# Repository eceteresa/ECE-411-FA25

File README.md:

# ECE 411 Fall 2025 Capstone
Hi hello! Welcome to our capstone. Please review software tools used and some tutorials for how to use said tools. :D

## Tools!

Here are the basic programs you'll need to have on your computer in order to interface with the projects:

- [VSCode](https://code.visualstudio.com/download): A helpful all-in-one programming IDE. Free!
      - You can install the [PlatformIO](https://docs.platformio.org/en/latest/integration/ide/vscode.html) extension and code .ino directly into the IDE!
- [Arduino IDE](https://www.arduino.cc/en/software/): If you would rather not use VSCode.
- Github: Not required, but _strongly_ recommended for ease of file sharing between machines. You can even work from your repo within VSCode using git bash!

### Github Onboarding Crash Course

[Github Setup](https://docs.github.com/en/get-started/git-basics/set-up-git)

[Using Git Graphical User Interface (GUI)](https://www.geeksforgeeks.org/git/working-on-git-for-gui/)

[Github markdown text cheat sheet](https://docs.github.com/en/get-started/writing-on-github/getting-started-with-writing-and-formatting-on-github/basic-writing-and-formatting-syntax)

[What are Git branches and why are they important](https://git-scm.com/book/en/v2/Git-Branching-Branches-in-a-Nutshell)

### Github Task Tracker

[Git Project Tracker Tutorial](https://docs.github.com/en/issues/planning-and-tracking-with-projects/learning-about-projects/quickstart-for-projects)
This tutorial should help you get familiar with how to use the task tracking board under "Projects" in the linked menu up above. There is a kanban template available, so it mimics what Trello can do almost exactly, if not better. The table layout was used so that it's a little easier to see who is assigned to what, and as I (Teresa) poke around with the task tracker it should be pretty intuitive to assign tasks and whatnot. And we don't have to worry about the Trello contributor limit for free accounts.

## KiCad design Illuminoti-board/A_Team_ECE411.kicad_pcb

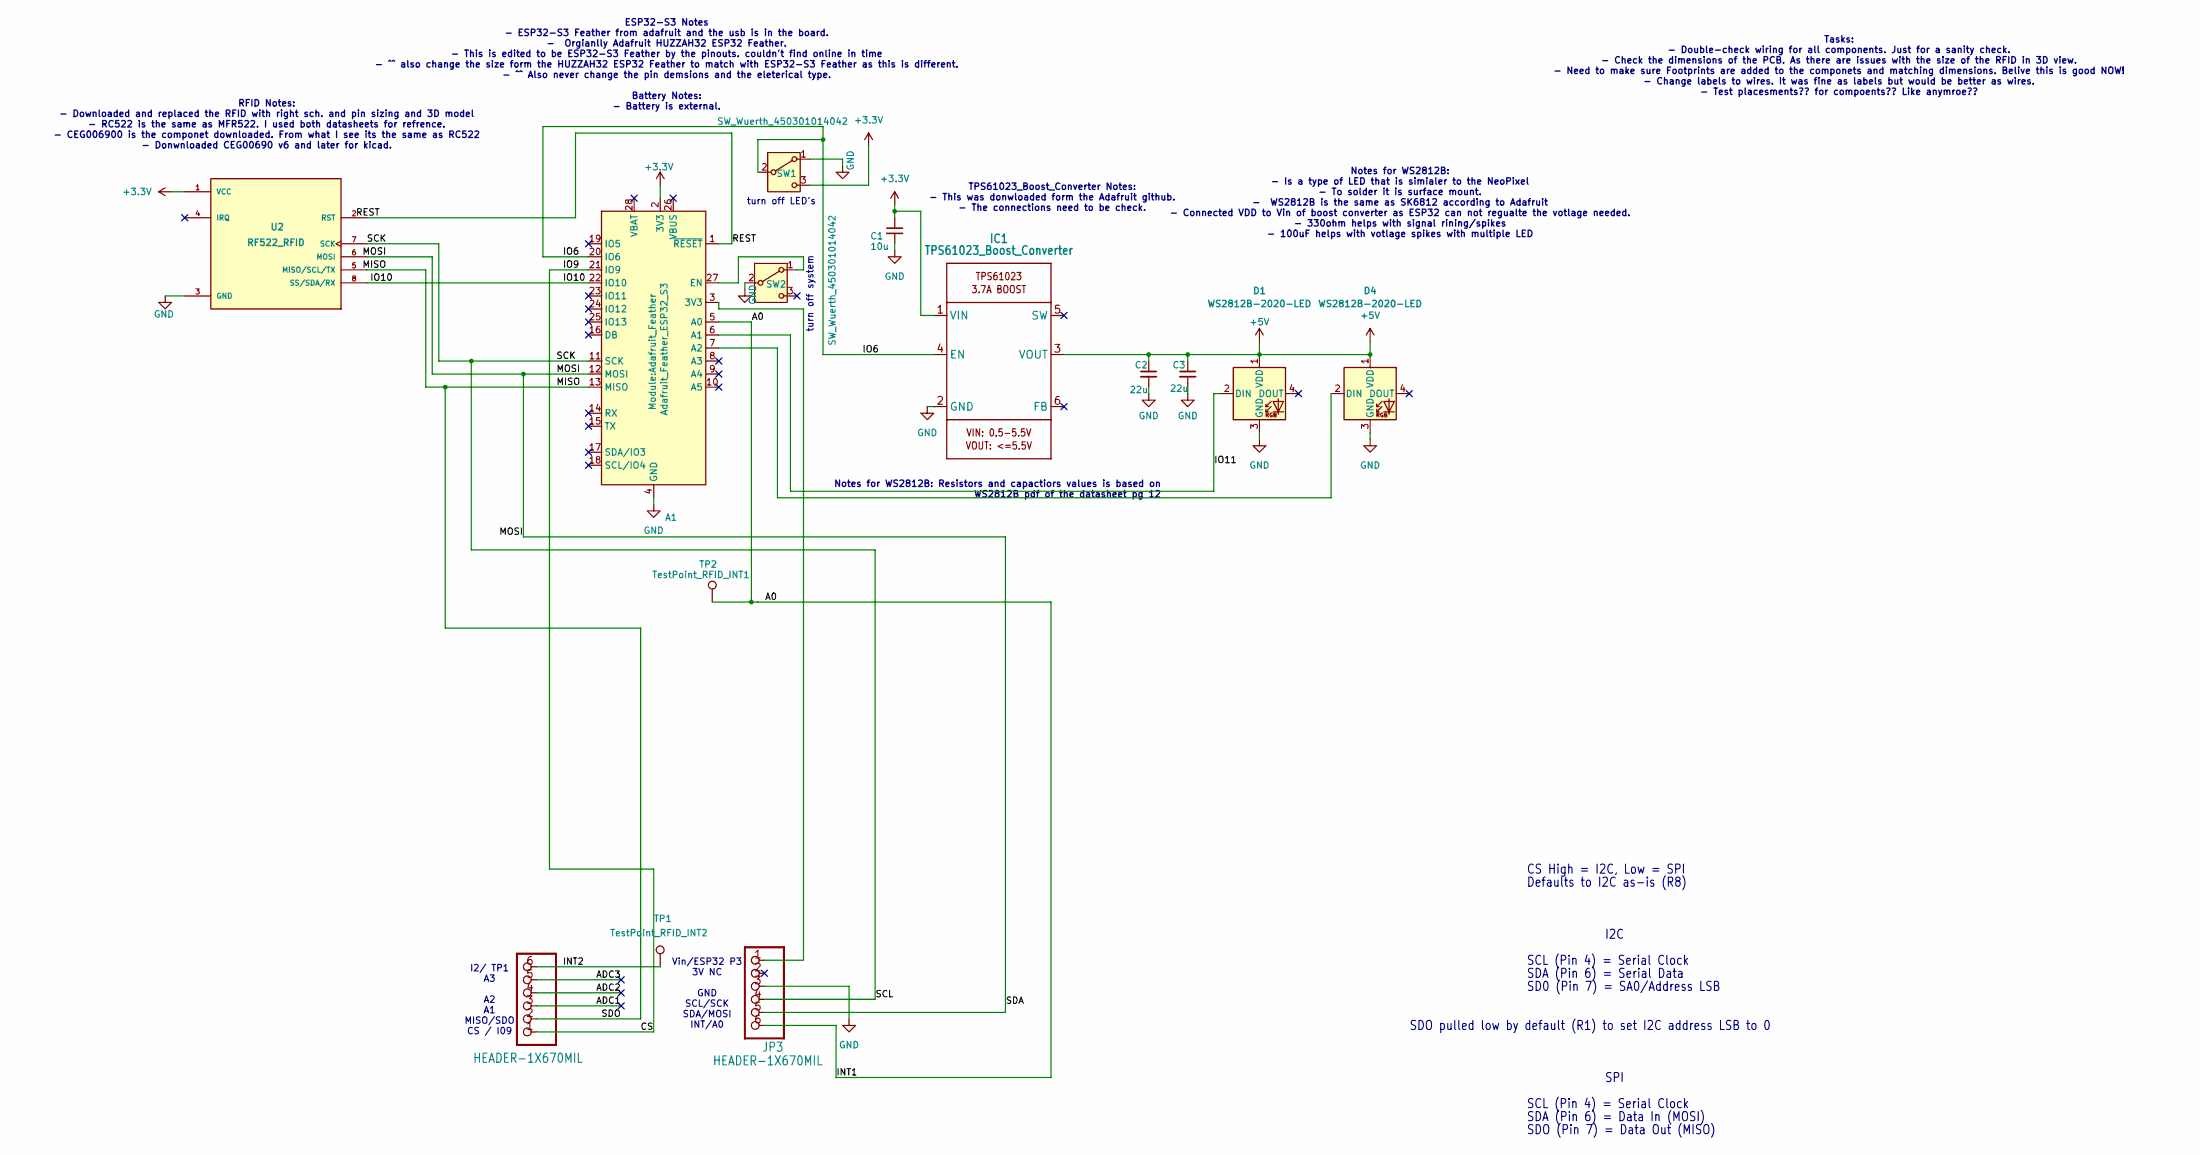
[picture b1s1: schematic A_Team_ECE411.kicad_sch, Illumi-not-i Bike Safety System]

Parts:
A1: Adafruit_Feather_ESP32_S3; Adafruit_Feather
C1: 10u; C_1206_3216Metric_Pad1.33x1.80mm_HandSolder; Part number 399-15735-2-ND
C2, C3: 22u; C_1206_3216Metric_Pad1.33x1.80mm_HandSolder; Part number 581-KGM31AR71A226MU
D1, D4: WS2812B-2020-LED; PinHeader_1x03_P2.54mm_Vertical; Part number 2552
IC1: TPS61023_Boost_Converter; PinHeader_1x04_P2.54mm_Vertical; Part number 4654
JP2, JP3: HEADER-1X670MIL; PinHeader_1x06_P2.54mm_Vertical
SW1, SW2: SW_Wuerth_450301014042; PinHeader_1x03_P2.54mm_Vertical
TP1: TestPoint_RFID_INT2; TestPoint_THTPad_1.0x1.0mm_Drill0.5mm
TP2: TestPoint_RFID_INT1; TestPoint_THTPad_1.0x1.0mm_Drill0.5mm
U2: RF522_RFID; PinHeader_1x08_P2.54mm_Vertical; PARTREV 12 June 2019

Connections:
+3.3V: A1.2 (3V3), C1.1, IC1.1 (VIN), SW1.3 (3V), U2.1 (VCC)
+5V: C2.1, C3.1, D1.1 (VDD), D4.1 (VDD), IC1.3 (VOUT)
/A0: A1.5 (A0), JP3.6, TP2.1
/ADC1: JP2.3
/ADC2: JP2.4
/ADC3: JP2.5
/CS: A1.21 (IO9), JP2.1
/INT2: JP2.6, TP1.1
/IO6: A1.20 (IO6), IC1.4 (EN), SW1.2 (B)
/IO10: A1.22 (IO10), U2.8 (SS/SDA/RX)
/IO11: A1.6 (A1), D1.2 (DIN)
/MISO: A1.13 (MISO), JP2.2, U2.5 (MISO/SCL/TX)
/MOSI: A1.12 (MOSI), JP3.5, U2.6 (MOSI)
/REST: A1.1 (~RESET), U2.2 (RST)
/SCK: A1.11 (SCK), JP3.4, U2.7 (SCK)
GND: A1.4 (GND), C1.2, C2.2, C3.2, D1.3 (GND), D4.3 (GND), IC1.2 (GND), JP3.3, SW1.1 (GND), SW2.2 (B), U2.3 (GND)
unnamed: A1.3 (3V3), JP3.1
unnamed: A1.7 (A2), D4.2 (DIN)
unnamed: A1.27 (EN), SW2.1 (A)

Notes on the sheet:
Tasks: - Double-check wiring for all components. Just for a sanity check. - Check the dimensions of the PCB. As there are issues with the size of the RFID in 3D view. - Need to make sure Footprints are added to the componets and matching dimensions. Belive this is good NOW! - Change labels to wires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
SDO (Pin 7) = Data Out (MISO)
SDA (Pin 6) = Data In (MOSI)
SCL (Pin 4) = Serial Clock
I2/ TP1 A3 A2 A1 MISO/SDO CS / I09
SPI
SD0 (Pin 7) = SA0/Address LSB
ESP32-S3 Notes - ESP32-S3 Feather from adafruit and the usb is in the board. - Orgianlly Adafruit HUZZAH32 ESP32 Feather. - This is edited to be ESP32-S3 Feather by the pinouts. couldn't find online in time - ^^ also change the size form the HUZZAH32 ESP32 Feather to match with ESP32-S3 Feather as 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
SDO pulled low by default (R1) to set I2C address LSB to 0
TPS61023_Boost_Converter Notes: - This was donwloaded form the Adafruit github. - The connections need to be check.
Notes for WS2812B: - Is a type of LED that is simialer to the NeoPixel - To solder it is surface mount. - WS2812B is the same as SK6812 according to Adafruit - Connected VDD to Vin of boost converter as ESP32 can not regualte the votlage needed. - 330ohm helps with signal rining/spikes - 100uF help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
Vin/ESP32 P3 3V NC GND SCL/SCK SDA/MOSI INT/A0
Defaults to I2C as-is (R8)
SDA (Pin 6) = Serial Data
turn off LED's
turn off system
Notes for WS2812B: Resistors and capactiors values is based on WS2812B pdf of the datasheet pg 12
CS High = I2C, Low = SPI
RFID Notes: - Downloaded and replaced the RFID with right sch. and pin sizing and 3D model - RC522 is the same as MFR522. I used both datasheets for refrence. - CEG006900 is the componet downloaded. From what I see its the same as RC522 - Donwnloaded CEG00690 v6 and later for kicad.
I2C

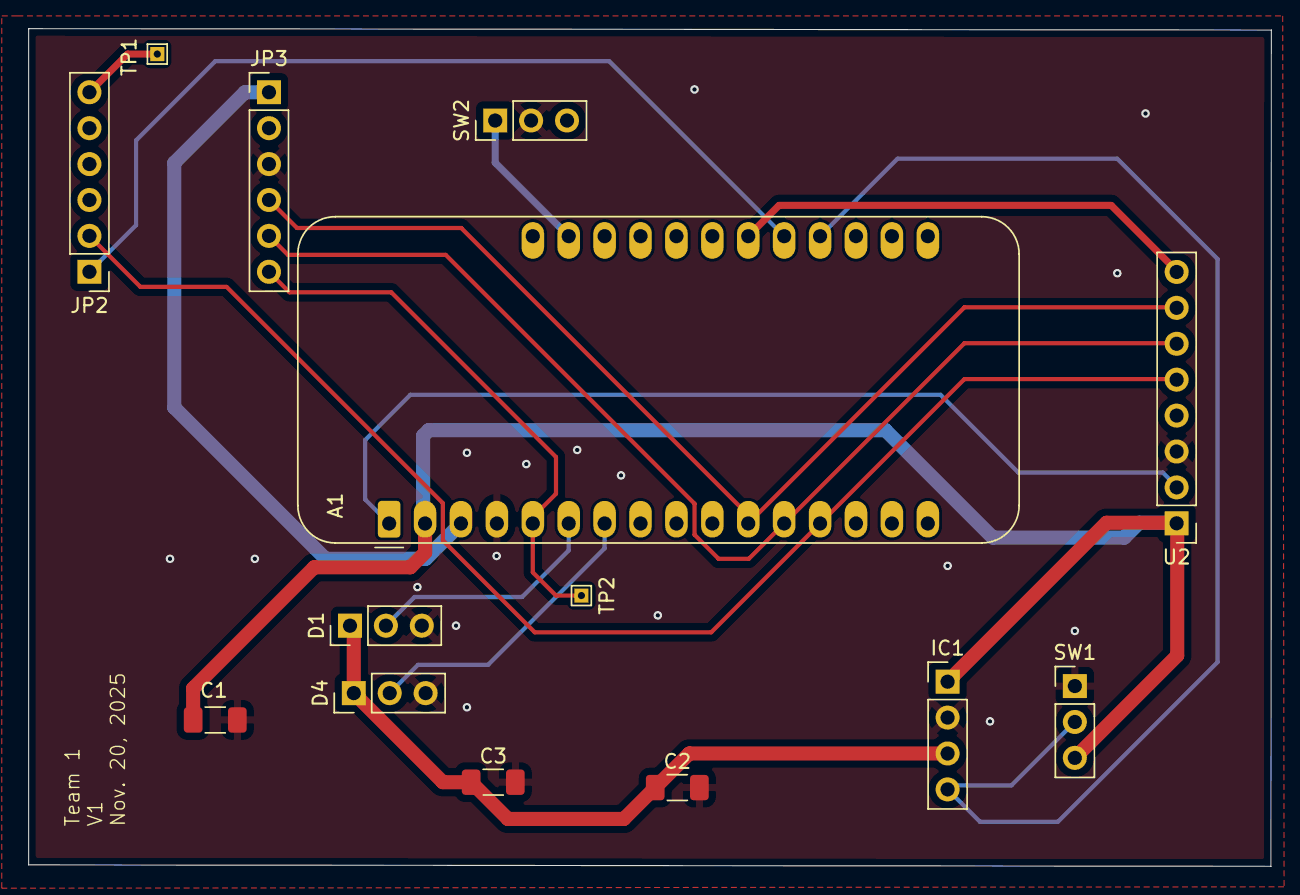
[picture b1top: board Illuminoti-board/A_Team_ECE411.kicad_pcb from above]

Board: 2 copper layers, 87.9 x 59.2 mm, 14 parts (0 on the bottom side), 16 nets.

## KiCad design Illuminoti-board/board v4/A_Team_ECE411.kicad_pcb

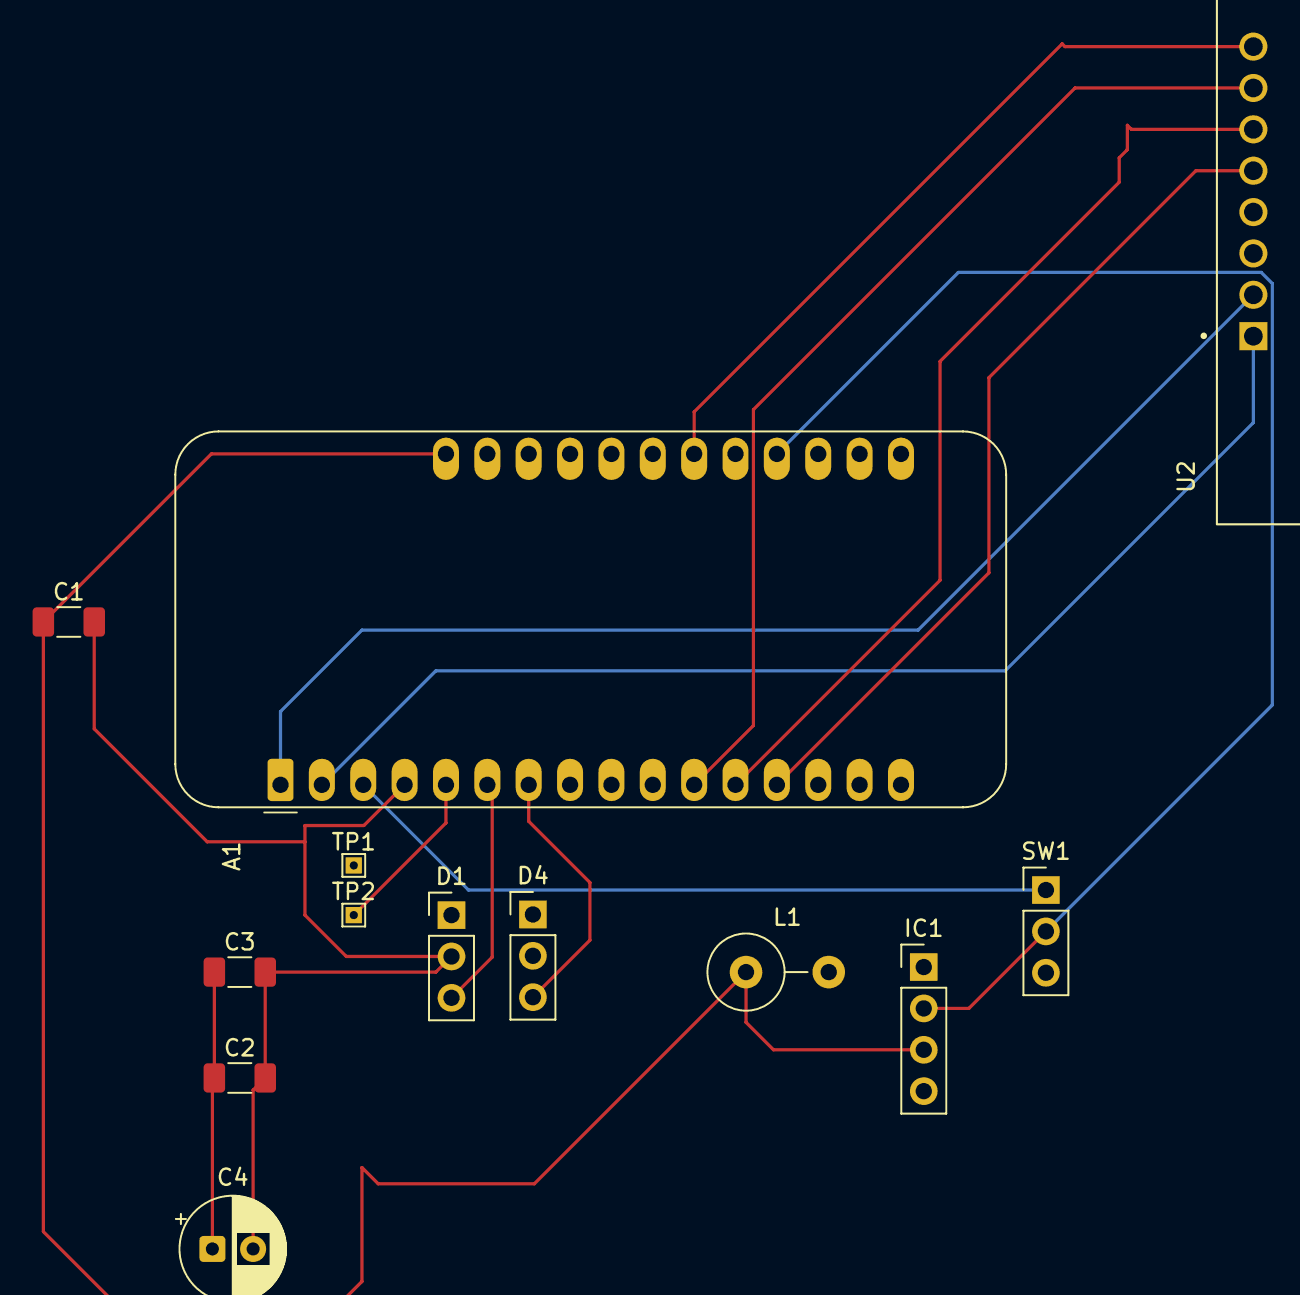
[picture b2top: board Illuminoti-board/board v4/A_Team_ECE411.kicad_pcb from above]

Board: 2 copper layers, 13 parts (0 on the bottom side), 14 nets.

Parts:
A1: Adafruit_Feather_ESP32_S3; Adafruit_Feather
C1: 10u; C_1206_3216Metric_Pad1.33x1.80mm_HandSolder
C2, C3: 22u; C_1206_3216Metric_Pad1.33x1.80mm_HandSolder
C4: 100u; CP_Radial_D6.3mm_P2.50mm
D1, D4: WS2812B-2020-LED; PinHeader_1x03_P2.54mm_Vertical
IC1: TPS61023_Boost_Converter; PinHeader_1x04_P2.54mm_Vertical
L1: 1u; L_Axial_L11.0mm_D4.5mm_P5.08mm_Vertical_Fastron_MECC
SW1: SW_Wuerth_450301014042; PinHeader_1x03_P2.54mm_Vertical
TP1: TestPoint_RFID_INT2; TestPoint_THTPad_1.0x1.0mm_Drill0.5mm
TP2: TestPoint_RFID_INT1; TestPoint_THTPad_1.0x1.0mm_Drill0.5mm
U2: RF522_RFID; MODULE_CEG006900

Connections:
+3.3V: A1.2 (3V3), U2.1 (VCC)
+5V: C2.1, C3.1, C4.1
+BATT: A1.28 (VBAT), C1.1, IC1.3 (VIN), L1.1
/A0: A1.5 (A0), TP2.1
/IO6: A1.20 (IO6), IC1.2 (EN), SW1.2 (C)
/IO10: A1.22 (IO10), U2.8 (SS/SDA/RX)
/IO11: A1.6 (A1), D1.3 (DIN)
/MISO: A1.13 (MISO), U2.5 (MISO/SCL/TX)
/MOSI: A1.12 (MOSI), U2.6 (MOSI)
/REST: A1.1 (~RESET), U2.2 (RST)
/SCK: A1.11 (SCK), U2.7 (SCK)
GND: A1.4 (GND), C1.2, C2.2, C3.2, C4.2, D1.2 (VSS), D4.2 (VSS), IC1.4 (GND), SW1.3 (A), U2.3 (GND)
unnamed: A1.7 (A2), D4.3 (DIN)
unnamed: A1.3 (3V3), SW1.1 (B)

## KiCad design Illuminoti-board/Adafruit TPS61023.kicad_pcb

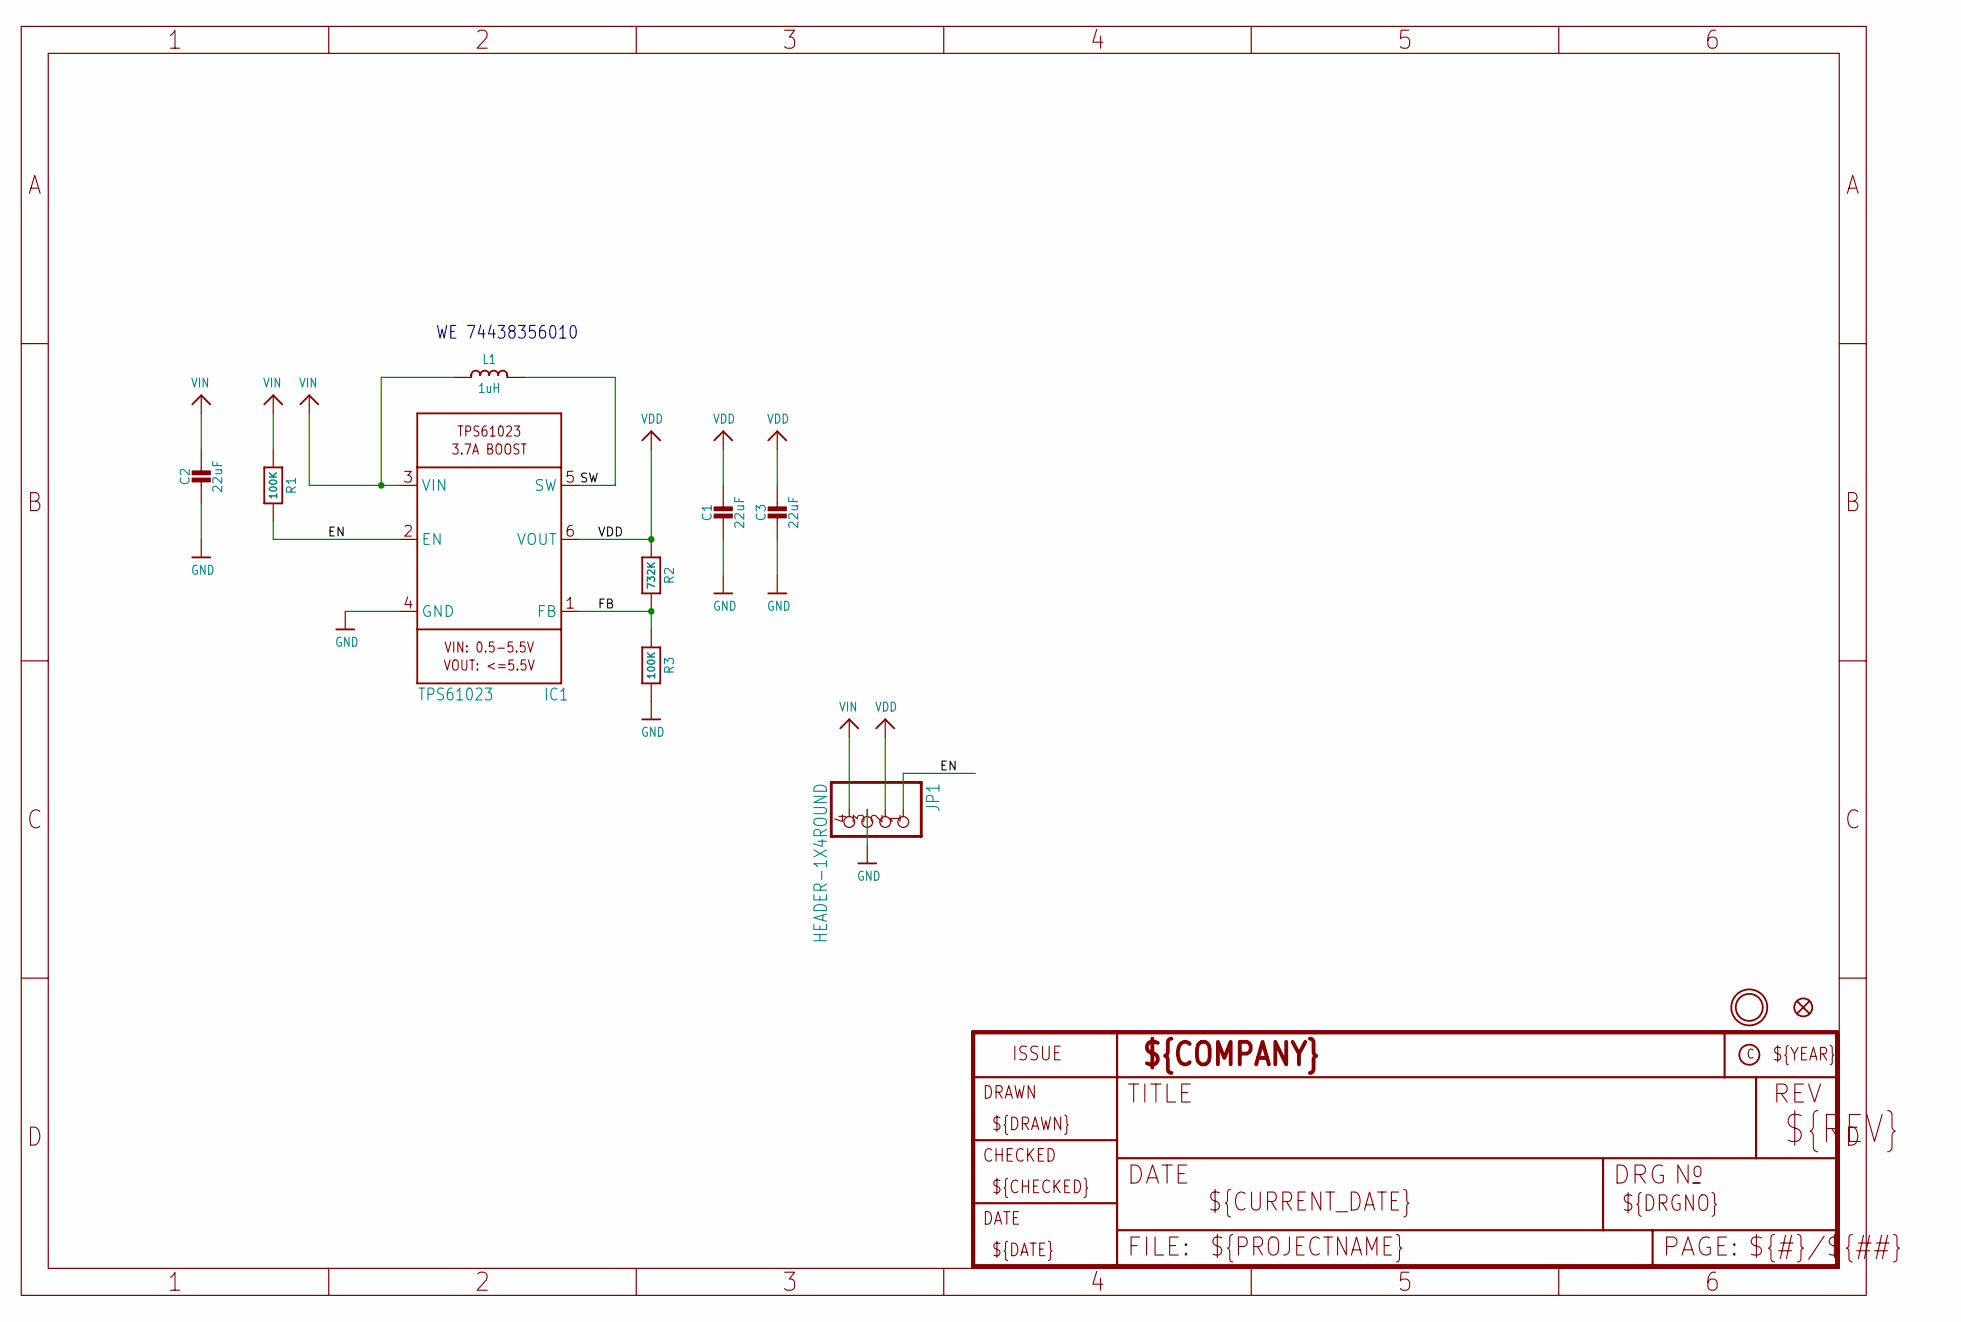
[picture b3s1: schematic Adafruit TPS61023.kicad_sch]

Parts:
C1, C2, C3: 22uF; 0805-NO
FID1: FIDUCIAL_1MM
IC1: TPS61023; SOT563
JP1: HEADER-1X4ROUND; 1X04_ROUND
L1: 1uH; INDUCTOR_5X5MM_TDK_VLC5045
R1, R3: 100K; 0603-NO
R2: 732K; 0603-NO
U$9: MOUNTINGHOLE2.5; MOUNTINGHOLE_2.5_PLATED

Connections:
EN: IC1.2 (EN), JP1.1, R1.2
FB: IC1.1 (FB), R2.2, R3.1
GND: C1.2, C2.2, C3.2, IC1.4 (GND), JP1.3, R3.2
SW: IC1.5 (SW), L1.P$2 (2)
VDD: C1.1, C3.1, IC1.6 (VOUT), JP1.2, R2.1
VIN: C2.1, IC1.3 (VIN), JP1.4, L1.P$1 (1), R1.1

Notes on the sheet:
WE 74438356010

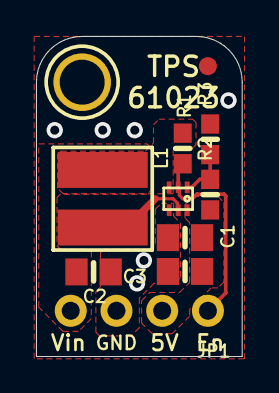
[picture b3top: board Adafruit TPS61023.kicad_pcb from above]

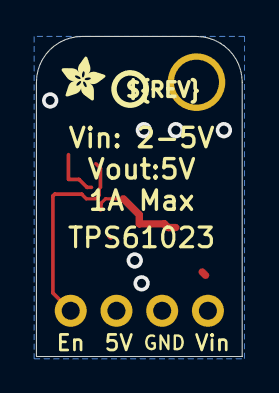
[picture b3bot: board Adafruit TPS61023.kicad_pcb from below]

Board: 2 copper layers, 11.4 x 17.8 mm, 13 parts (2 on the bottom side), 6 nets.

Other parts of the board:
U$10: PCBFEAT-REV-040
U$11: ADAFRUIT_2.5MM

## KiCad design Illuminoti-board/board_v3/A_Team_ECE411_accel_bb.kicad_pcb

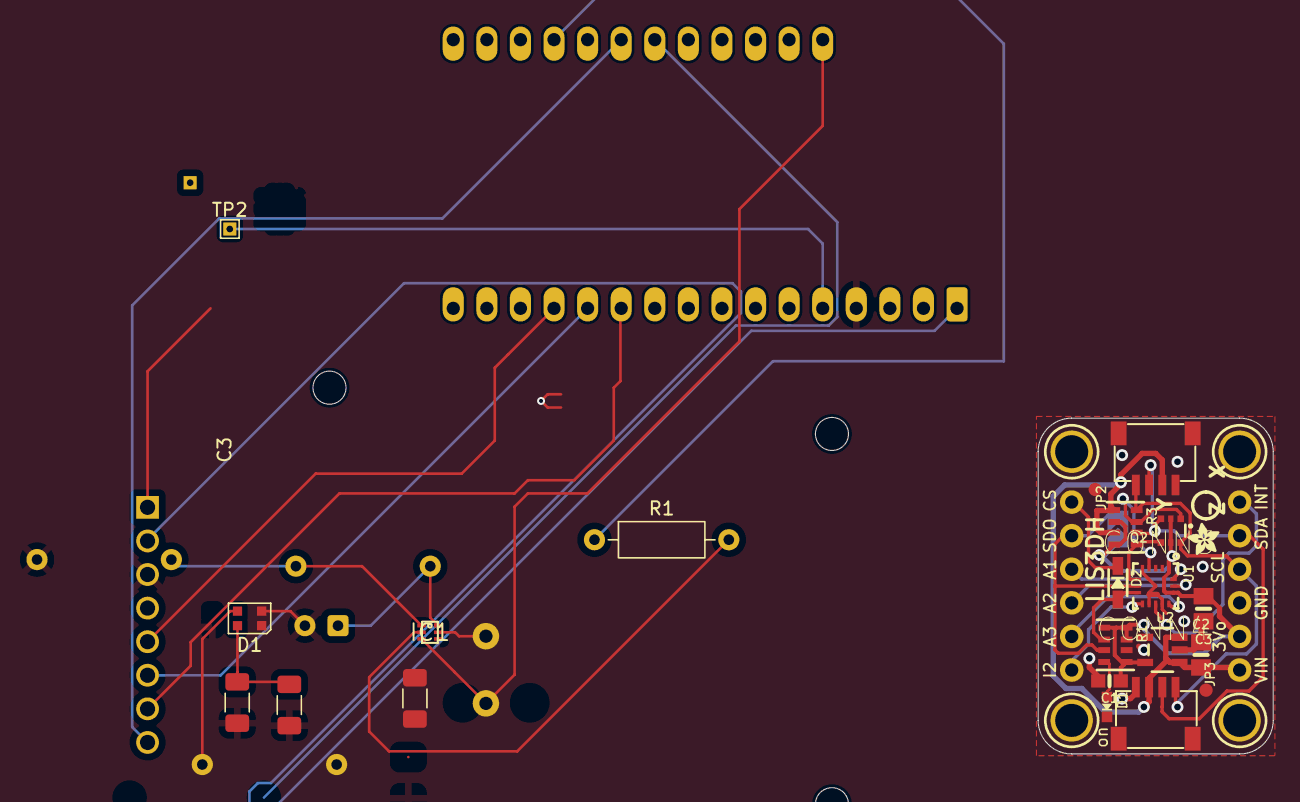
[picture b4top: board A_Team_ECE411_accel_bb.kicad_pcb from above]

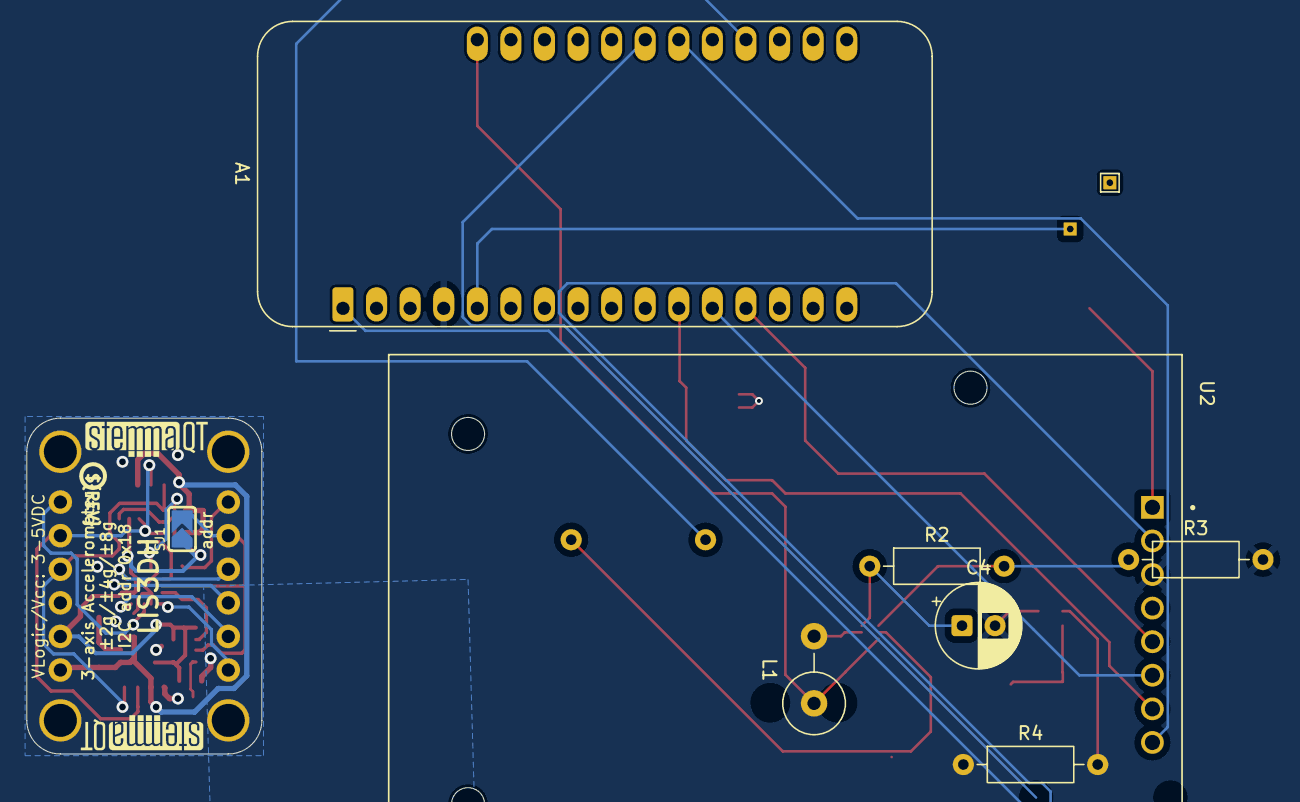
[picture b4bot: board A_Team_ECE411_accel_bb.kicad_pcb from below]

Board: 2 copper layers, 17.8 x 25.4 mm, 40 parts (12 on the bottom side), 31 nets.

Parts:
A1: Adafruit_Feather_ESP32_S3; Adafruit_Feather
C1: 0.1uF; 0603-NO
C1#2: 10u; C_1206_3216Metric_Pad1.33x1.80mm_HandSolder
C2, C3#2: 22u; C_1206_3216Metric_Pad1.33x1.80mm_HandSolder
C2#2, C3: 10uF; 0805-NO
C4: 100u; CP_Radial_D6.3mm_P2.50mm
CONN3, CONN4: STEMMA_I2C_QT; JST_SH4
D1: GREEN; CHIPLED_0603_NOOUTLINE
D1#2: WS2812B-2020-LED; LED_WS2812B-2020_PLCC4_2.0x2.0mm
D2: 1N4148; SOD-323
FID3, FID4: FIDUCIAL_1MM
IC1: TPS61023_Boost_Converter; SOT563
JP2, JP3: 1X06_ROUND_70
L1: 1u; L_Axial_L11.0mm_D4.5mm_P5.08mm_Vertical_Fastron_MECC
Q2: BSS138; SOT363
R1: 10k; R_Axial_DIN0207_L6.3mm_D2.5mm_P10.16mm_Horizontal
R1#2, R3: 10K; RESPACK_4X0603
R2: 723k; R_Axial_DIN0207_L6.3mm_D2.5mm_P10.16mm_Horizontal
R3#2: 100k; R_Axial_DIN0207_L6.3mm_D2.5mm_P10.16mm_Horizontal
R4: 330; R_Axial_DIN0207_L6.3mm_D2.5mm_P10.16mm_Horizontal
SJ1: SOLDERJUMPER_ARROW_NOPASTE
TP1: TestPoint_RFID_INT2; TestPoint_THTPad_1.0x1.0mm_Drill0.5mm
TP2: TestPoint_RFID_INT1; TestPoint_THTPad_1.0x1.0mm_Drill0.5mm
U1: LIS3DHTR; LGA16_3X3MM
U2: AP2112K-3.3; SOT23-5
U2#2: RF522_RFID; MODULE_CEG006900
U$1, U$17, U$19, U$21: MOUNTINGHOLE2.5; MOUNTINGHOLE_2.5_PLATED
U$12: ADAFRUIT_2.5MM
U$25: PCBFEAT-REV-040
U$30, U$31: STEMMAQT

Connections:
3.3V: C1.1, C3.1, JP3.2, Q2.2, Q2.5, R1#2.1, R1#2.5, R1#2.7, R1#2.8, R3.2, R3.4, SJ1.1, U1.1, U1.14, U2.5
+3.3V: A1.2 (3V3), U2#2.1 (VCC)
+5V: C2.1, C3#2.1, C4.1, D1#2.4 (VDD), IC1.6 (VOUT), R2.1
+BATT: A1.28 (VBAT), C1#2.1, IC1.3 (VIN), L1.1
/A0: A1.5 (A0), TP2.1
/IO6: A1.20 (IO6), R1.1
/IO10: A1.22 (IO10), U2#2.8 (SS/SDA/RX)
/IO11: A1.23 (IO11), R4.1
/MISO: A1.13 (MISO), U2#2.5 (MISO/SCL/TX)
/MOSI: A1.12 (MOSI), U2#2.6 (MOSI)
/REST: A1.1 (~RESET), U2#2.2 (RST)
/SCK: A1.11 (SCK), U2#2.7 (SCK)
ADC1: JP2.3, U1.16
ADC2: JP2.4, U1.15
ADC3: JP2.5, U1.13
CS: D2.C, JP2.1
GND: A1.4 (GND), C1.2, C1#2.2, C2.2, C2#2.2, C3.2, C3#2.2, C4.2, CONN3.1, CONN4.1, D1.C, D1#2.2 (VSS), IC1.4 (GND), JP3.3, R1#2.6, R3#2.2, U1.5, U1.10, U1.12, U2.2, U2#2.3 (GND)
INT1: JP3.6, U1.11
INT2: JP2.6, U1.9
unnamed: D1.A, R1#2.4
unnamed: D2.A, R1#2.2, U1.8
unnamed: D1#2.3 (DIN), R4.2
unnamed: IC1.2 (EN), R1.2
unnamed: IC1.1 (FB), R2.2, R3#2.1
unnamed: IC1.5 (SW), L1.2
SCL: CONN3.4, CONN4.4, JP3.4, Q2.6, R3.8
SCL_3V: Q2.1, R3.7, U1.4
SDA: CONN3.3, CONN4.3, JP3.5, Q2.3, R3.6
SDA_3V: Q2.4, R3.5, U1.6
SDO: JP2.2, R1#2.3, SJ1.2, U1.7
VCC: C2#2.1, CONN3.2, CONN4.2, JP3.1, R3.1, R3.3, U2.1, U2.3

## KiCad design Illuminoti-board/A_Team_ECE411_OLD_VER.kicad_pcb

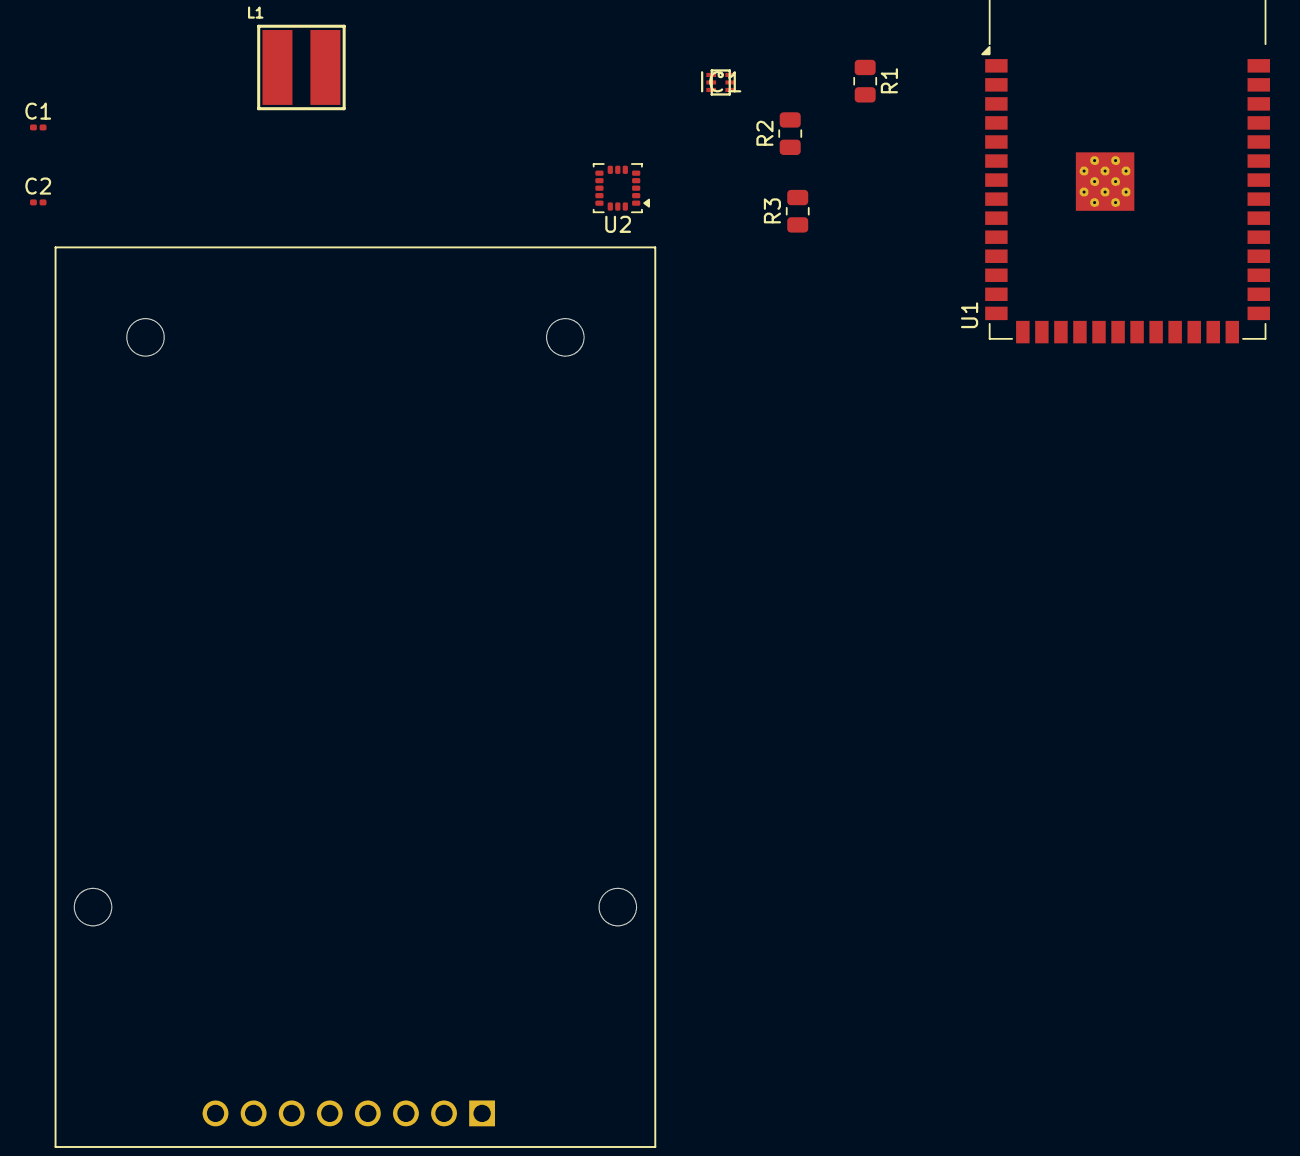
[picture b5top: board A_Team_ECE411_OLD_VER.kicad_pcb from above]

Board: 2 copper layers, 10 parts (0 on the bottom side), 13 nets, no tracks yet.

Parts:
C1: 10u; C_0201_0603Metric
C2: 44u; C_0201_0603Metric
IC1: TPS61023_Boost_Converter; SOT563
L1: 1u; INDUCTOR_5X5MM_TDK_VLC5045
R1: 10k; R_0805_2012Metric
R2: 732k; R_0805_2012Metric
R3: 100k; R_0805_2012Metric
U1: ESP32-S3-WROOM-1
U2: LIS3DH_Accelerator; LGA-16_3x3mm_P0.5mm_LayoutBorder3x5y
U3: RF522_RFID; MODULE_CEG006900

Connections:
+5V: C2.1, IC1.6 (VOUT), R2.1
/IRQ: U1.21 (IO13), U3.4 (IRQ)
/MOSI: U1.19 (IO11), U3.6 (MOSI)
/SCK: U1.20 (IO12), U3.7 (SCK)
/SCL: U1.17 (IO9), U2.4 (SPC), U3.5 (MISO/SCL/TX)
/SDA: U1.12 (IO8), U2.6 (SDI), U3.8 (SS/SDA/RX)
GND: C1.2, C2.2, IC1.4 (GND), R3.2, U1.1 (GND), U1.40 (GND), U1.41 (GND), U2.5 (GND), U2.7 (SDO), U2.10 (GND), U2.12 (GND), U3.3 (GND)
unnamed: IC1.2 (EN), R1.1
unnamed: IC1.1 (FB), R2.2, R3.1
unnamed: IC1.5 (SW), L1.P$2 (2)
unnamed: C1.1, IC1.3 (VIN), L1.P$1 (1), U1.2 (3V3), U2.1 (VDD_IO), U2.14 (VDD), U3.1 (VCC)
unnamed: R1.2, U1.3 (EN)
unnamed: U1.27 (IO0), U3.2 (RST)

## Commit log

2025-10-02 setting up directory things
2025-10-16 updating README
2025-10-16 adding PDS template
2025-11-06 Add files via upload
    Here's our HW6 breadboard progress report
2025-11-09 adding platformio stuff
2025-11-11 adding scripts
2025-11-11 adding test hex print
2025-11-11 adding spreadsheet
2025-11-18 adding details for project
2025-11-19 Rename A_Team_ECE411.kicad_sch to A_Team_ECE411_OLDVER.kicad_sch
2025-11-19 Rename A_Team_ECE411.kicad_pcb to A_Team_ECE411_OLDVER.kicad_pcb
2025-11-19 Rename A_Team_ECE411.kicad_sch to A_Team_ECE411_OLDERVER2.kicad_sch
2025-11-19 Create OLDER_Kicad_Files
2025-11-19 Rename A_Team_ECE411_OLDERVER2.kicad_sch to A_Team_ECE411_OLDER_VER.kicad_sch
2025-11-19 Rename A_Team_ECE411_OLDVER.kicad_pcb to A_Team_ECE411_OLD_VER.kicad_pcb
2025-11-19 Add files via upload
    Here's the code I have to test proper connection the LIS3DH and the RFID to our ESP32s.
2025-11-19 Add files via upload
    Here's our most recent wiring diagram for our breadboard! Will update if/when things change.
2025-11-20 Create BOM
2025-11-20 Add files via upload
    updated wiring diagram to include our surface mount caps
2025-11-20 Rename _wiringDiagram_rev2.png to 411wiringDiagram_rev2.png
2025-11-20 Add files via upload
    Most recent schematic and pcb files. The footprint for the accelerometer is the most urgent thing to be adjusted and then general cleanup could be helpful if time allows.
2025-11-21 adding iterations of Illuminoti board
2025-11-23 Add files via upload
    edited footprints, resolved DRC errors
2025-11-23 Add files via upload
    updated schematic pdf with edited symbols, resolved DRC errors
2025-11-23 Add files via upload
    gerber files for jcl pcb order
2025-11-25 Add link about Git branches to README
    Added a link explaining Git branches and their importance.
2025-11-26 working RFID badge script. detects which badge has been hard coded, which badge has not
2025-11-26 adding slide show images for HW10 description
2025-11-29 Create lights_setup.ino
    initial code used to test controlling two different neopixel strips seperately
2025-11-29 Add files via upload
    Here's a test code for the LEDs, code is fully commented for clarity. Let me know if you have any questions, or need any help testing! - Cass
2025-12-01 Add files via upload
    corrected headlight and taillight colors
2025-12-04 testing NeoPixel strip for RFID
2025-12-04 adding PlatformIO test project
    adding PlatformIO test project to test logic
2025-12-04 adding HW10 test plan to git repo
2025-12-04 re-locating PlatformIO project so I can open it within VSCode
2025-12-04 Accept file deletions from src after relocating project
2025-12-04 changing var names to script
2025-12-04 adding line changes
2025-12-05 adding notes to RFID_taps.ino and ensuring PlatformIO compilation on my laptop
2025-12-06 flow diagram for final script RD
2025-12-11 adding version 1.2 for integration test script
2025-12-11 adding Savannah test file
2025-12-11 adding updates to RFID_taps project
2025-12-11 Update LED code V1-2
2025-12-11 added .DS_Store to .gitignore
2025-12-11 correct healight and taillight colors
    headlights = white and tail lights = red
2025-12-11 added current integration, and subsystem test scripts for LEDs and accellerometer
2025-12-12 adding working scripts
2025-12-12 adding wire configs and components list
2025-12-12 file!
